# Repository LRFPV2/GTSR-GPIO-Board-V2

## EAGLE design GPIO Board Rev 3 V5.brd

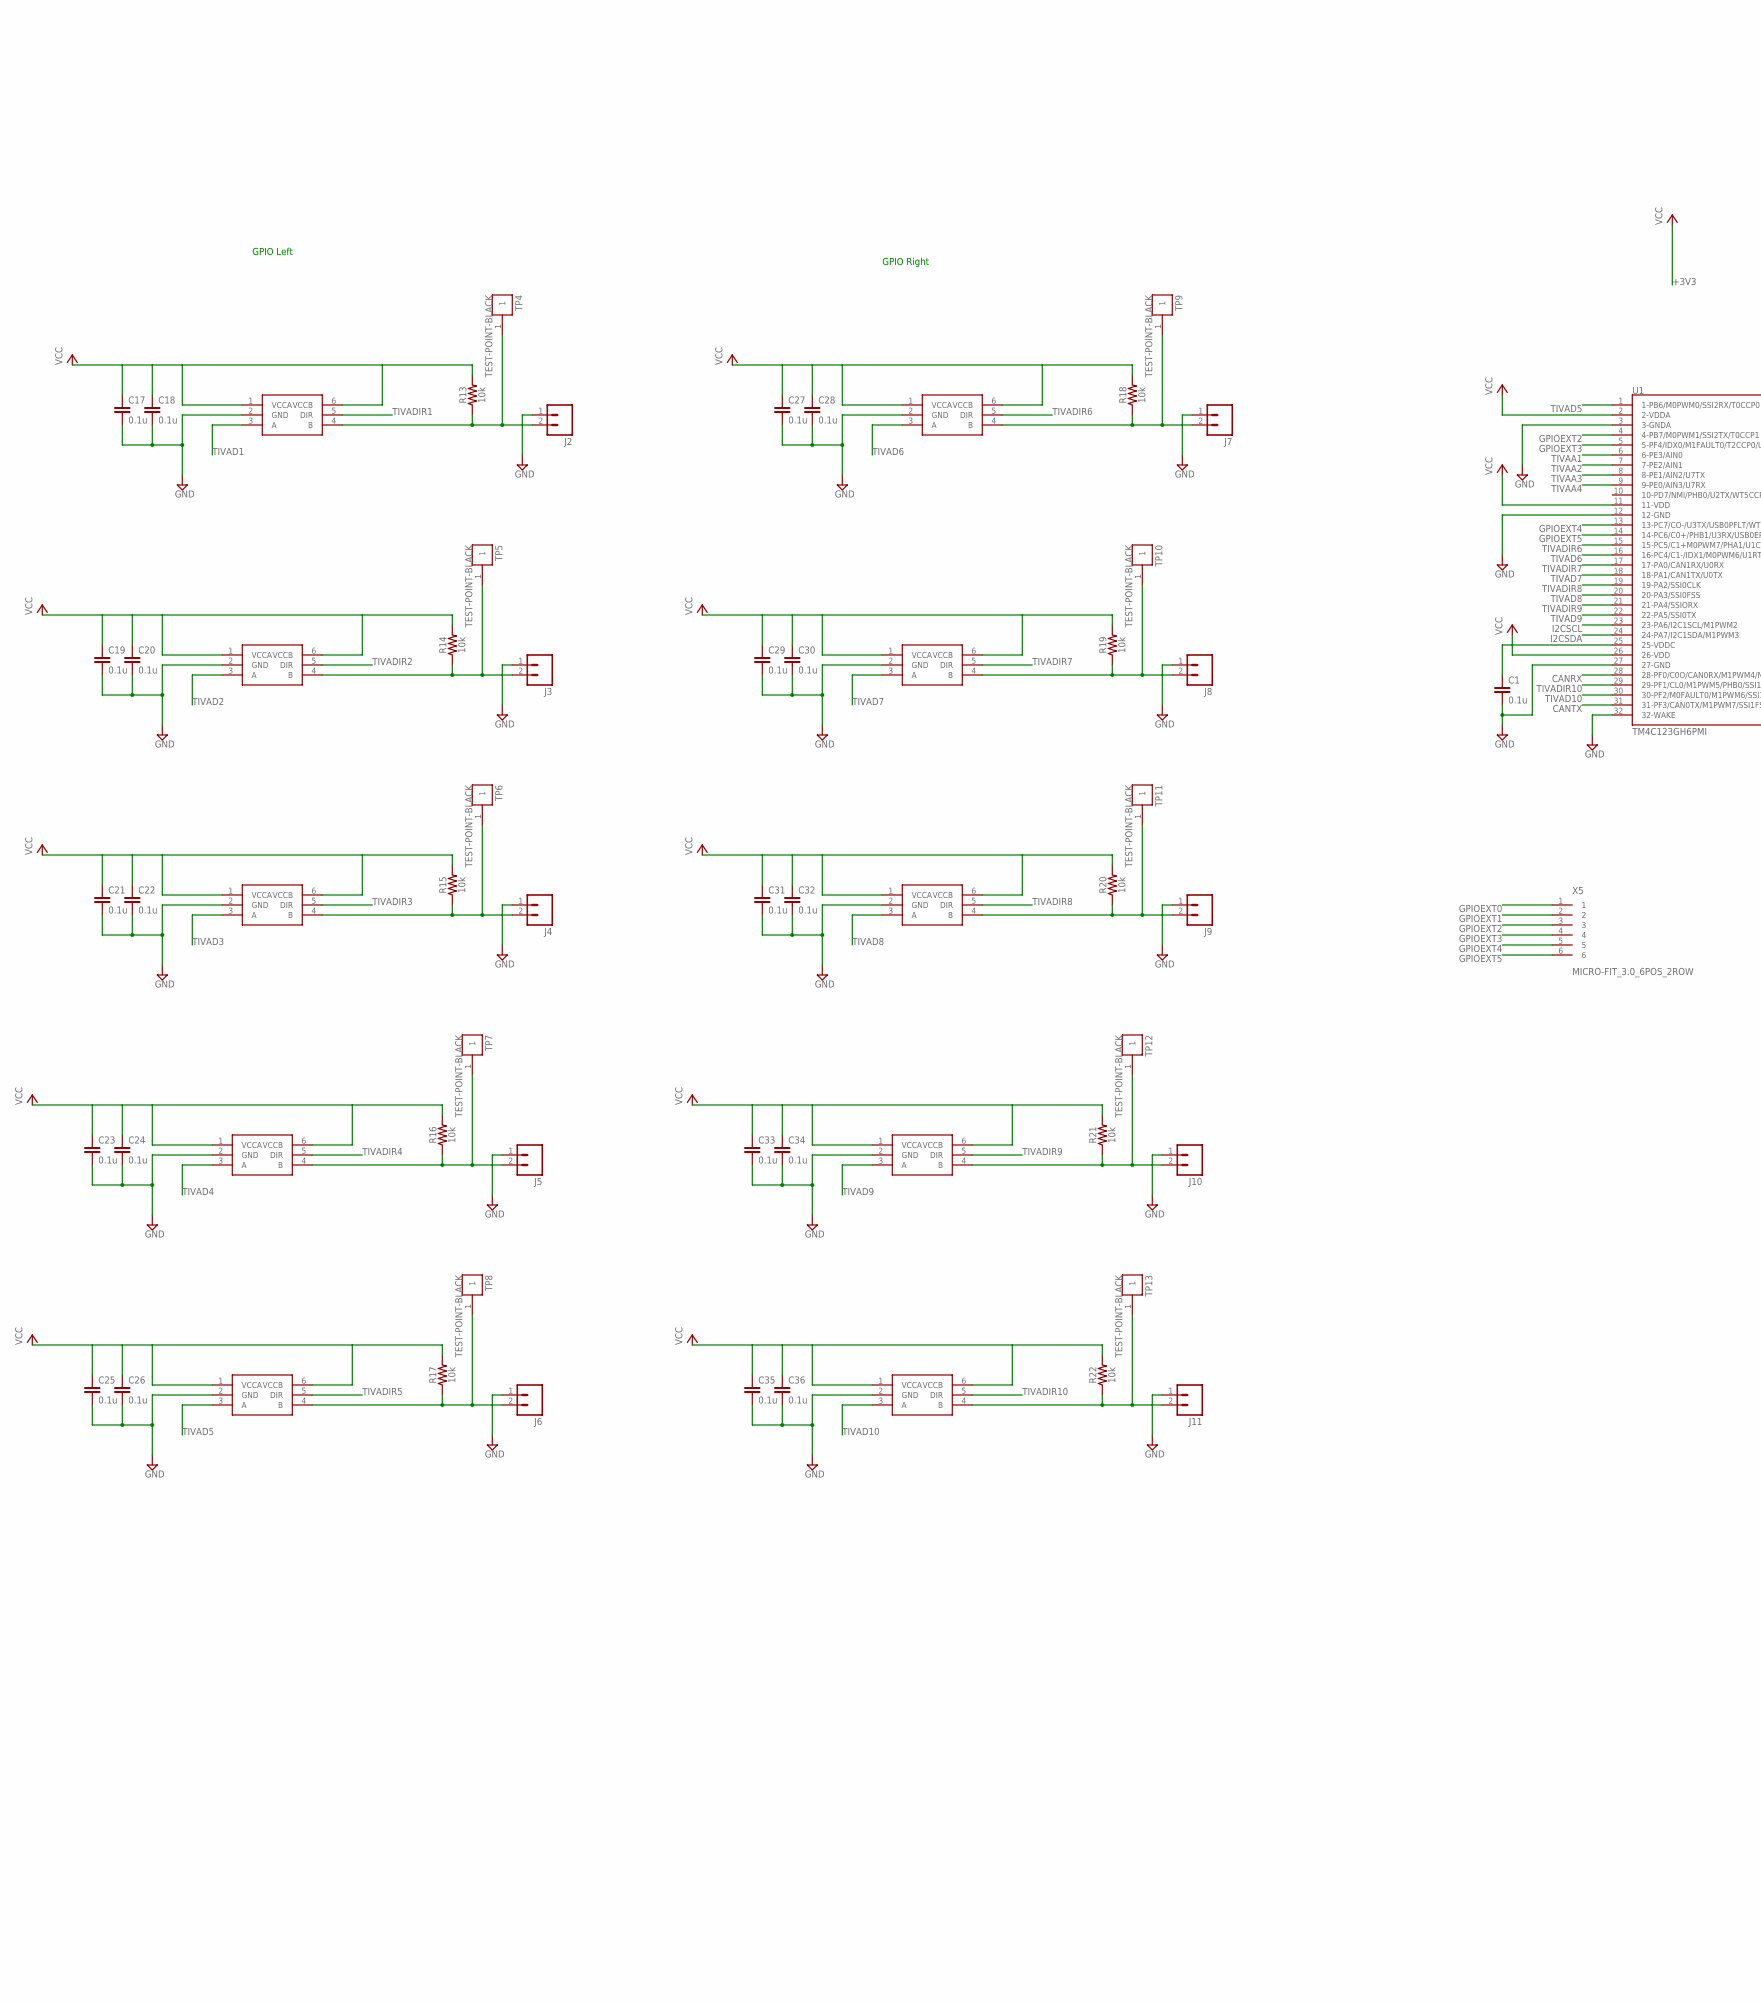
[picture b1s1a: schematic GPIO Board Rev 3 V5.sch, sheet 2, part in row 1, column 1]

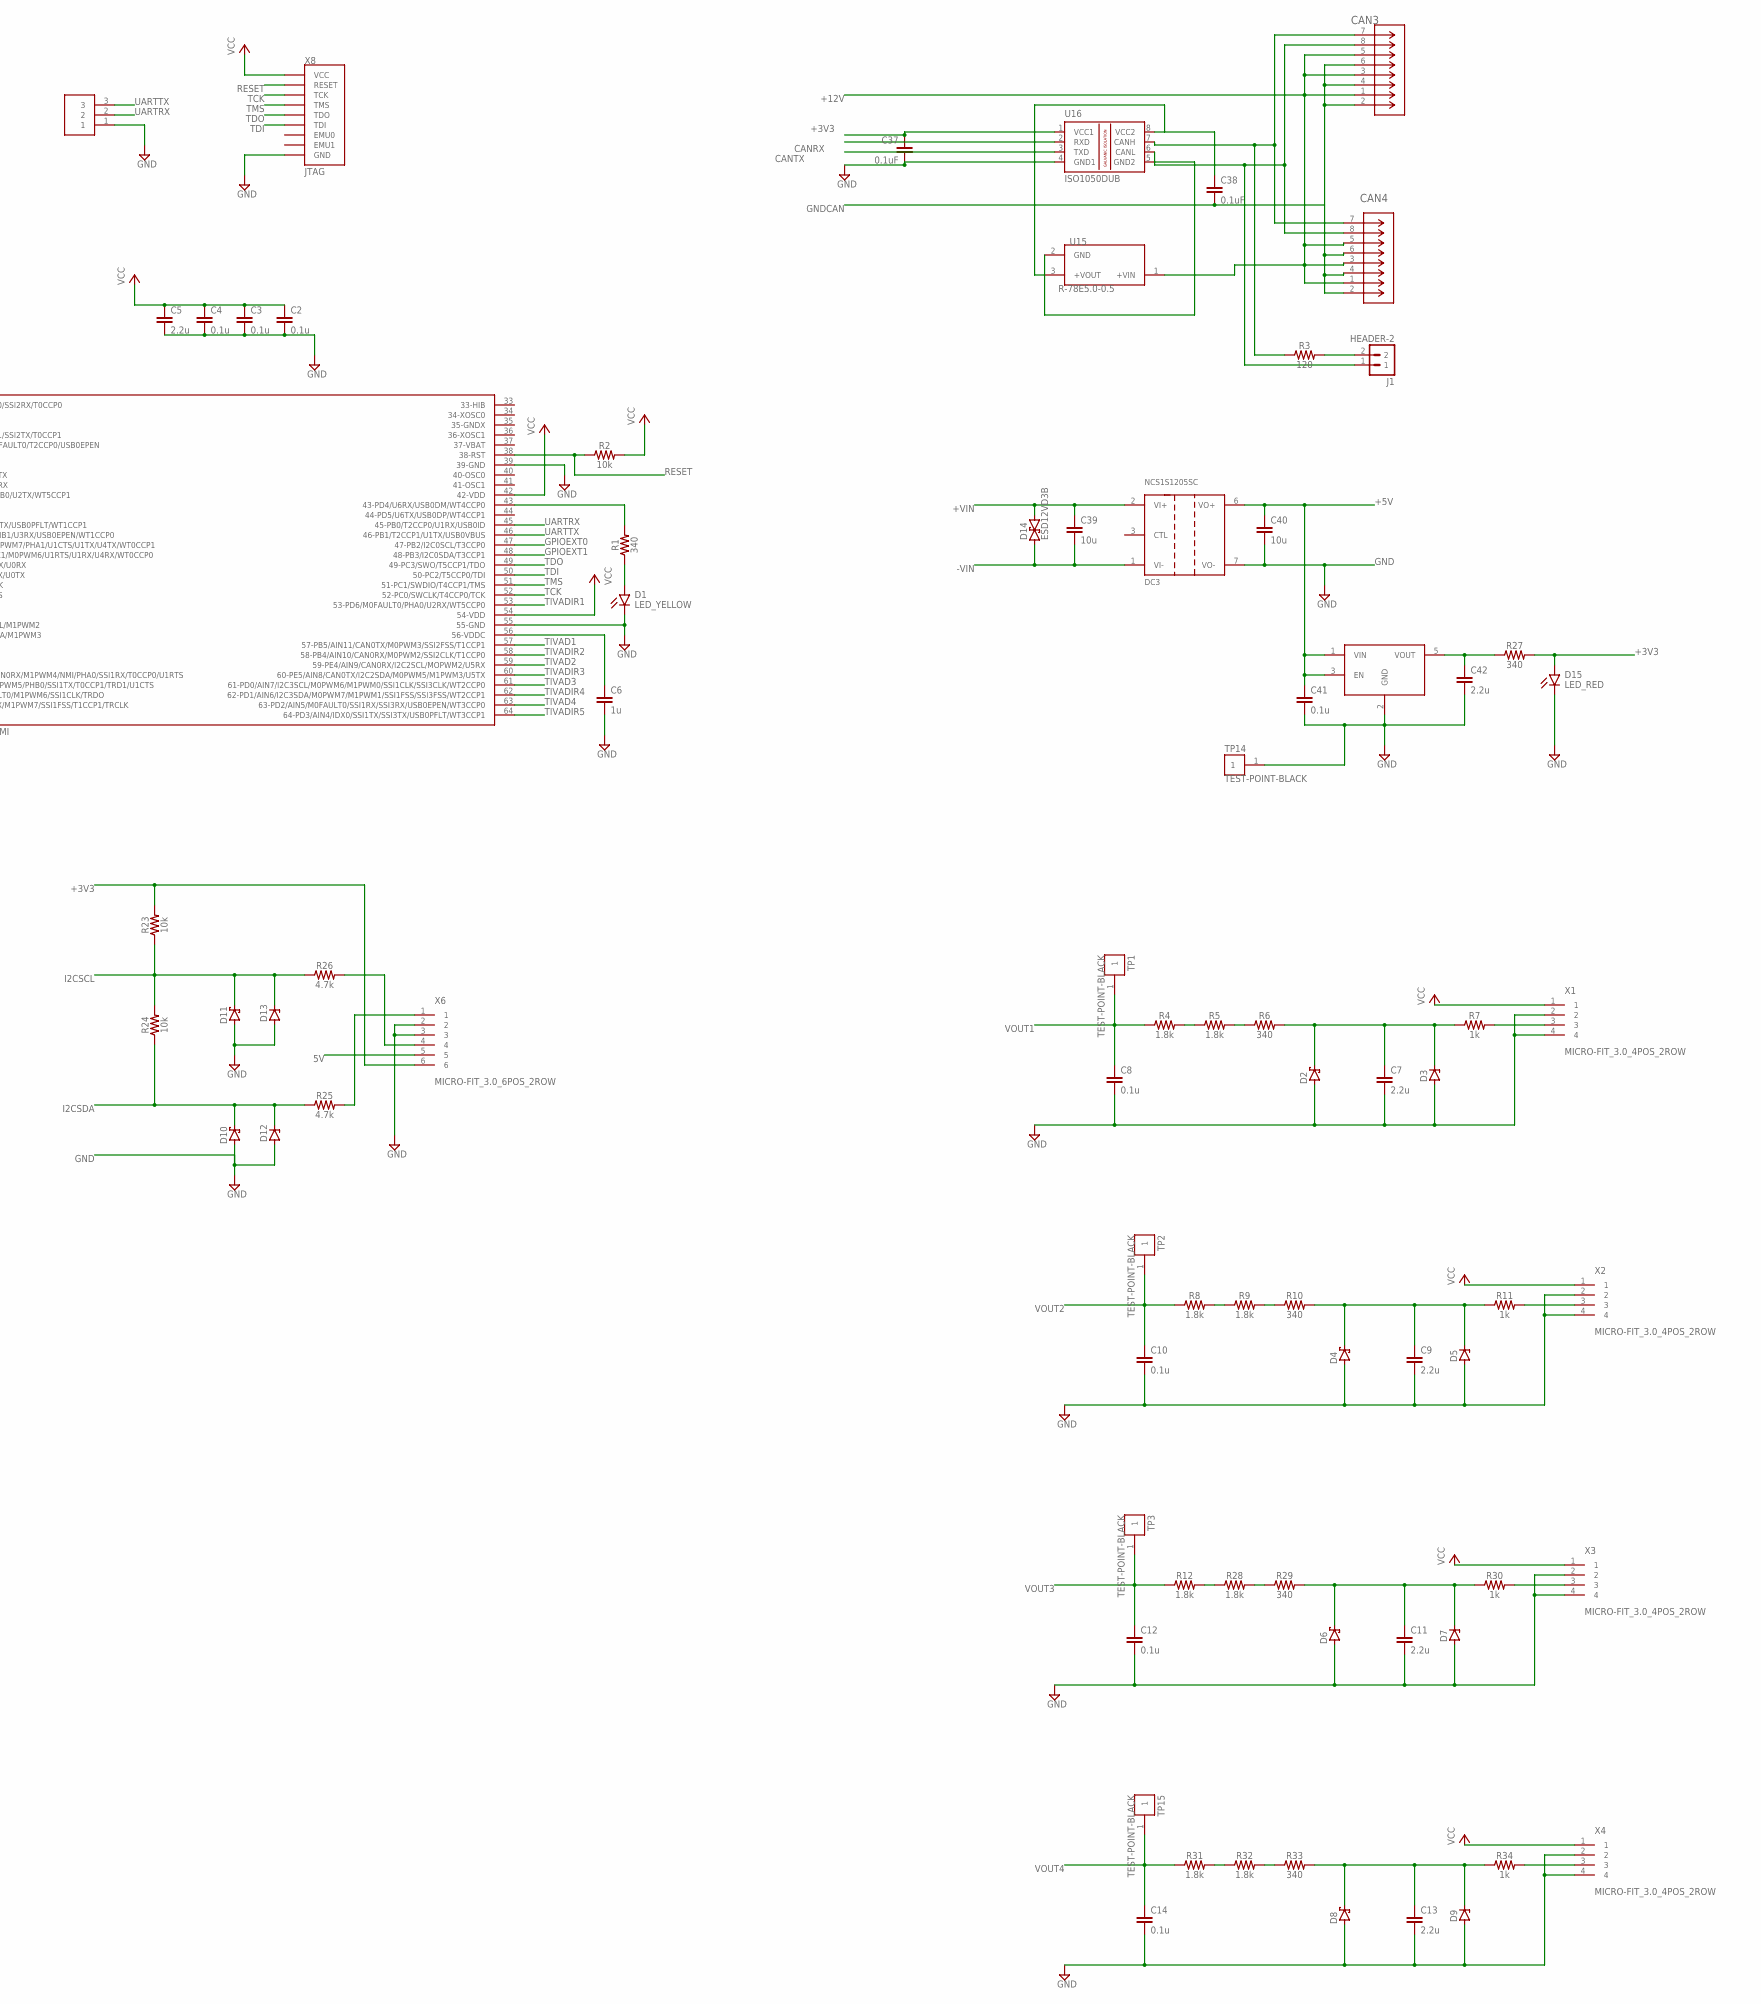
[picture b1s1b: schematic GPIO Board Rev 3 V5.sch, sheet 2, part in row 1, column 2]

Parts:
C1, C2, C3, C4, C8, C10, C12, C14, C41: 0.1u; C0603
C5, C7, C9, C11, C13: 2.2u; C0603
C6: 1u; C0603
C17, C18, C19, C20, C21, C22, C23, C24, C25, C26, C27, C28, C29, C30, C31, C32, C33, C34, C35, C36: 0.1u; C0402
C37: 0.1uF; C5B3.5
C38: 0.1uF; C2.5-4
C39, C40: 10u; 1206
C42: 2.2u; 0603
CAN3, CAN4: A-2004-2-4-LPS-N-R; CONN_4-LPS-N-R_ASM
D1: LED_YELLOW; LEDC1608X35N_FLAT-Y
D2, D4, D6, D8, D10, D11: SCHOTTKY-DIODESMD; SMB
D3, D5, D7, D9: ZENER-DIODESMB; SMB
D12, D13: ZENER-DIODESOT23; SOT23
D14: ESD12VD3B; SOD23
D15: LED_RED; LEDC2012X110N_FLAT-R
DC3: NCS1S1205SC; 7-SIP
DC4: NCV551SN33T1G; SOT23-5
J1: HEADER-2; HEADER-V-1X2
J2, J3, J4, J5, J6, J7, J8, J9, J10, J11: M02-JST-2-PTH-NO_SILK; JST-2-PTH-NS
R1, R6, R10, R27, R29, R33: 340; R0603
R2, R23, R24: 10k; R0603
R3: 120; R0603
R4, R5, R8, R9, R12, R28, R31, R32: 1.8k; R0603
R7, R11, R30, R34: 1k; R0603
R13, R14, R15, R16, R17, R18, R19, R20, R21, R22: 10k; 0603
R25, R26: 4.7k; R0603
TP1, TP2, TP3, TP4, TP5, TP6, TP7, TP8, TP9, TP10, TP11, TP12, TP13, TP14, TP15: TEST-POINT-BLACK; KEYSTONE_5001_0
U1: TM4C123GH6PMI; S-PQFP-G64
U5, U6, U7, U8, U9, U10, U11, U12, U13, U14: SN74LVC1T45-Q1; SC70
U15: R-78E5.0-0.5; CONV_R-78E5.0-0.5
U16: ISO1050DUB; DUB-R-PDSO-G8
U$2: HEADER-3; HEADER-V-1X3
X1, X2, X3, X4: MICRO-FIT_3.0_4POS_2ROW; 0430450412
X5, X6: MICRO-FIT_3.0_6POS_2ROW; 0430450612
X8: JTAG; HEADER-V-2X7

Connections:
5V: X6.5
+3V3: C37.2, D15.A, R23.2, R27.2, U16.1 (VCC1), X6.6
+5V: C40.1, C41.1, DC3.6 (VO+), DC4.1 (VIN), DC4.3 (EN)
+12V: CAN3.1, CAN3.3, CAN3.5, CAN4.1, CAN4.3, CAN4.5, U15.1 (+VIN)
+VIN: C39.1, D14.2, DC3.2 (VI+)
-VIN: C39.2, D14.1, DC3.1 (VI-)
CANRX: U1.28 (28-PF0/C0O/CAN0RX/M1PWM4/NMI/PHA0/SSI1R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), U16.2 (RXD)
CANTX: U1.31 (31-PF3/CAN0TX/M1PWM7/SSI1FSS/T1CCP1/TRC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), U16.3 (TXD)
GND: C1.2, C2.2, C3.2, C4.2, C5.2, C6.2, C7.2, C8.2, C9.2, C10.2, C11.2, C12.2, C13.2, C14.2, C17.2, C18.2, C19.2, C20.2, C21.2, C22.2, C23.2, C24.2, C25.2, C26.2, C27.2, C28.2, C29.2, C30.2, C31.2, C32.2, C33.2, C34.2, C35.2, C36.2, C37.1, C40.2, C41.2, C42.2, D1.C, D2.A, D3.A, D4.A, D5.A, D6.A, D7.A, D8.A, D9.A, D10.A, D11.A, D12.1 (A), D13.1 (A), D15.C, DC3.7 (VO-), DC4.2 (GND), J2.1, J3.1, J4.1, J5.1, J6.1, J7.1, J8.1, J9.1, J10.1, J11.1, TP14.1, U1.3 (3-GNDA), U1.12 (12-GND), U1.27 (27-GND), U1.32 (32-WAKE), U1.39 (39-GND), U1.55 (55-GND), U5.2 (GND), U6.2 (GND), U7.2 (GND), U8.2 (GND), U9.2 (GND), U10.2 (GND), U11.2 (GND), U12.2 (GND), U13.2 (GND), U14.2 (GND), U16.4 (GND1), U$2.1, X1.2, X1.4, X2.2, X2.4, X3.2, X3.4, X4.2, X4.4, X6.2, X6.3, X8.4 (GND), X8.6 (GND), X8.8 (GND), X8.10 (GND), X8.12 (GND)
GNDCAN: C38.2, CAN3.2, CAN3.4, CAN3.6, CAN4.2, CAN4.4, CAN4.6
GPIOEXT0: U1.47 (47-PB2/I2C0SCL/T3CCP0), X5.1
GPIOEXT1: U1.48 (48-PB3/I2C0SDA/T3CCP1), X5.2
GPIOEXT2: U1.4 (4-PB7/M0PWM1/SSI2TX/T0CCP1), X5.3
GPIOEXT3: U1.5 (5-PF4/IDX0/M1FAULT0/T2CCP0/USB0EPEN), X5.4
GPIOEXT4: U1.13 (13-PC7/CO-/U3TX/USB0PFLT/WT1CCP1), X5.5
GPIOEXT5: U1.14 (14-PC6/C0+/PHB1/U3RX/USB0EPEN/WT1CCP0), X5.6
I2CSCL: D11.C, D13.3 (C), R23.1, R24.2, R26.1, U1.23 (23-PA6/I2C1SCL/M1PWM2)
I2CSDA: D10.C, D12.3 (C), R24.1, R25.1, U1.24 (24-PA7/I2C1SDA/M1PWM3)
unnamed: R1.2, U1.43 (43-PD4/U6RX/USB0DM/WT4CCP0)
unnamed: D1.A, R1.1
unnamed: J1.2, R3.2
unnamed: CAN3.7, CAN4.7, R3.1, U16.7 (CANH)
unnamed: C1.1, U1.25 (25-VDDC)
unnamed: CAN3.8, CAN4.8, J1.1, U16.6 (CANL)
unnamed: R7.2, X1.3
unnamed: C6.1, U1.56 (56-VDDC)
unnamed: C7.1, D2.C, D3.C, R6.2, R7.1
unnamed: R5.2, R6.1
unnamed: R4.2, R5.1
unnamed: R11.2, X2.3
unnamed: C9.1, D4.C, D5.C, R10.2, R11.1
unnamed: R9.2, R10.1
unnamed: R8.2, R9.1
unnamed: R30.2, X3.3
unnamed: C11.1, D6.C, D7.C, R29.2, R30.1
unnamed: R28.2, R29.1
unnamed: R12.2, R28.1
unnamed: R34.2, X4.3
unnamed: J2.2, R13.1, TP4.1, U5.4 (B)
unnamed: J7.2, R18.1, TP9.1, U10.4 (B)
unnamed: J3.2, R14.1, TP5.1, U6.4 (B)
unnamed: J4.2, R15.1, TP6.1, U7.4 (B)
unnamed: J5.2, R16.1, TP7.1, U8.4 (B)
unnamed: J8.2, R19.1, TP10.1, U11.4 (B)
unnamed: J6.2, R17.1, TP8.1, U9.4 (B)
unnamed: J9.2, R20.1, TP11.1, U12.4 (B)
unnamed: J10.2, R21.1, TP12.1, U13.4 (B)
unnamed: J11.2, R22.1, TP13.1, U14.4 (B)
unnamed: R26.2, X6.4
unnamed: R25.2, X6.1
unnamed: C13.1, D8.C, D9.C, R33.2, R34.1
unnamed: R32.2, R33.1
unnamed: U15.2 (GND), U16.5 (GND2)
unnamed: C38.1, U16.8 (VCC2)
unnamed: C42.1, DC4.5 (VOUT), R27.1
unnamed: R31.2, R32.1
RESET: R2.1, U1.38 (38-RST), X8.2 (RESET)
TCK: U1.52 (52-PC0/SWCLK/T4CCP0/TCK), X8.9 (TCK), X8.11 (TCK)
TDI: U1.50 (50-PC2/T5CCP0/TDI), X8.3 (TDI)
TDO: U1.49 (49-PC3/SWO/T5CCP1/TDO), X8.7 (TDO)
TIVAA1: U1.6 (6-PE3/AIN0)
TIVAA2: U1.7 (7-PE2/AIN1)
TIVAA3: U1.8 (8-PE1/AIN2/U7TX)
TIVAA4: U1.9 (9-PE0/AIN3/U7RX)
TIVAD1: U1.57 (57-PB5/AIN11/CAN0TX/M0PWM3/SSI2FSS/T1CC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), U5.3 (A)
TIVAD2: U1.59 (59-PE4/AIN9/CAN0RX/I2C2SCL/MOPWM2/U5RX), U6.3 (A)
TIVAD3: U1.61 (61-PD0/AIN7/I2C3SCL/M0PWM6/M1PWM0/SSI1C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), U7.3 (A)
TIVAD4: U1.63 (63-PD2/AIN5/M0FAULT0/SSI1RX/SSI3RX/USB0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), U8.3 (A)
TIVAD5: U1.1 (1-PB6/M0PWM0/SSI2RX/T0CCP0), U9.3 (A)
TIVAD6: U1.16 (16-PC4/C1-/IDX1/M0PWM6/U1RTS/U1RX/U4RX/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), U10.3 (A)
TIVAD7: U1.18 (18-PA1/CAN1TX/U0TX), U11.3 (A)
TIVAD8: U1.20 (20-PA3/SSI0FSS), U12.3 (A)
TIVAD9: U1.22 (22-PA5/SSI0TX), U13.3 (A)
TIVAD10: U1.30 (30-PF2/M0FAULT0/M1PWM6/SSI1CLK/TRDO), U14.3 (A)
TIVADIR1: U1.53 (53-PD6/M0FAULT0/PHA0/U2RX/WT5CCP0), U5.5 (DIR)
TIVADIR2: U1.58 (58-PB4/AIN10/CAN0RX/M0PWM2/SSI2CLK/T1CC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), U6.5 (DIR)
TIVADIR3: U1.60 (60-PE5/AIN8/CAN0TX/I2C2SDA/M0PWM5/M1PWM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), U7.5 (DIR)
TIVADIR4: U1.62 (62-PD1/AIN6/I2C3SDA/M0PWM7/M1PWM1/SSI1F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), U8.5 (DIR)
TIVADIR5: U1.64 (64-PD3/AIN4/IDX0/SSI1TX/SSI3TX/USB0PFLT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), U9.5 (DIR)
TIVADIR6: U1.15 (15-PC5/C1+M0PWM7/PHA1/U1CTS/U1TX/U4TX/W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), U10.5 (DIR)
TIVADIR7: U1.17 (17-PA0/CAN1RX/U0RX), U11.5 (DIR)
TIVADIR8: U1.19 (19-PA2/SSI0CLK), U12.5 (DIR)
TIVADIR9: U1.21 (21-PA4/SSIORX), U13.5 (DIR)
TIVADIR10: U1.29 (29-PF1/CL0/M1PWM5/PHB0/SSI1TX/T0CCP1/TR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), U14.5 (DIR)
TMS: U1.51 (51-PC1/SWDIO/T4CCP1/TMS), X8.1 (TMS)
UARTRX: U1.45 (45-PB0/T2CCP0/U1RX/USB0ID), U$2.2
UARTTX: U1.46 (46-PB1/T2CCP1/U1TX/USB0VBUS), U$2.3
VCC: C2.1, C3.1, C4.1, C5.1, C18.1, C20.1, C22.1, C24.1, C26.1, C28.1, C30.1, C32.1, C34.1, C36.1, R2.2, R13.2, R14.2, R15.2, R16.2, R17.2, R18.2, R19.2, R20.2, R21.2, R22.2, U1.2 (2-VDDA), U1.11 (11-VDD), U1.26 (26-VDD), U1.42 (42-VDD), U1.54 (54-VDD), U5.6 (VCCB), U6.6 (VCCB), U7.6 (VCCB), U8.6 (VCCB), U9.6 (VCCB), U10.6 (VCCB), U11.6 (VCCB), U12.6 (VCCB), U13.6 (VCCB), U14.6 (VCCB), X1.1, X2.1, X3.1, X4.1, X8.5 (VCC)
VOUT1: C8.1, R4.1, TP1.1
VOUT2: C10.1, R8.1, TP2.1
VOUT3: C12.1, R12.1, TP3.1
VOUT4: C14.1, R31.1, TP15.1

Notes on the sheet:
GPIO Left
GPIO Right

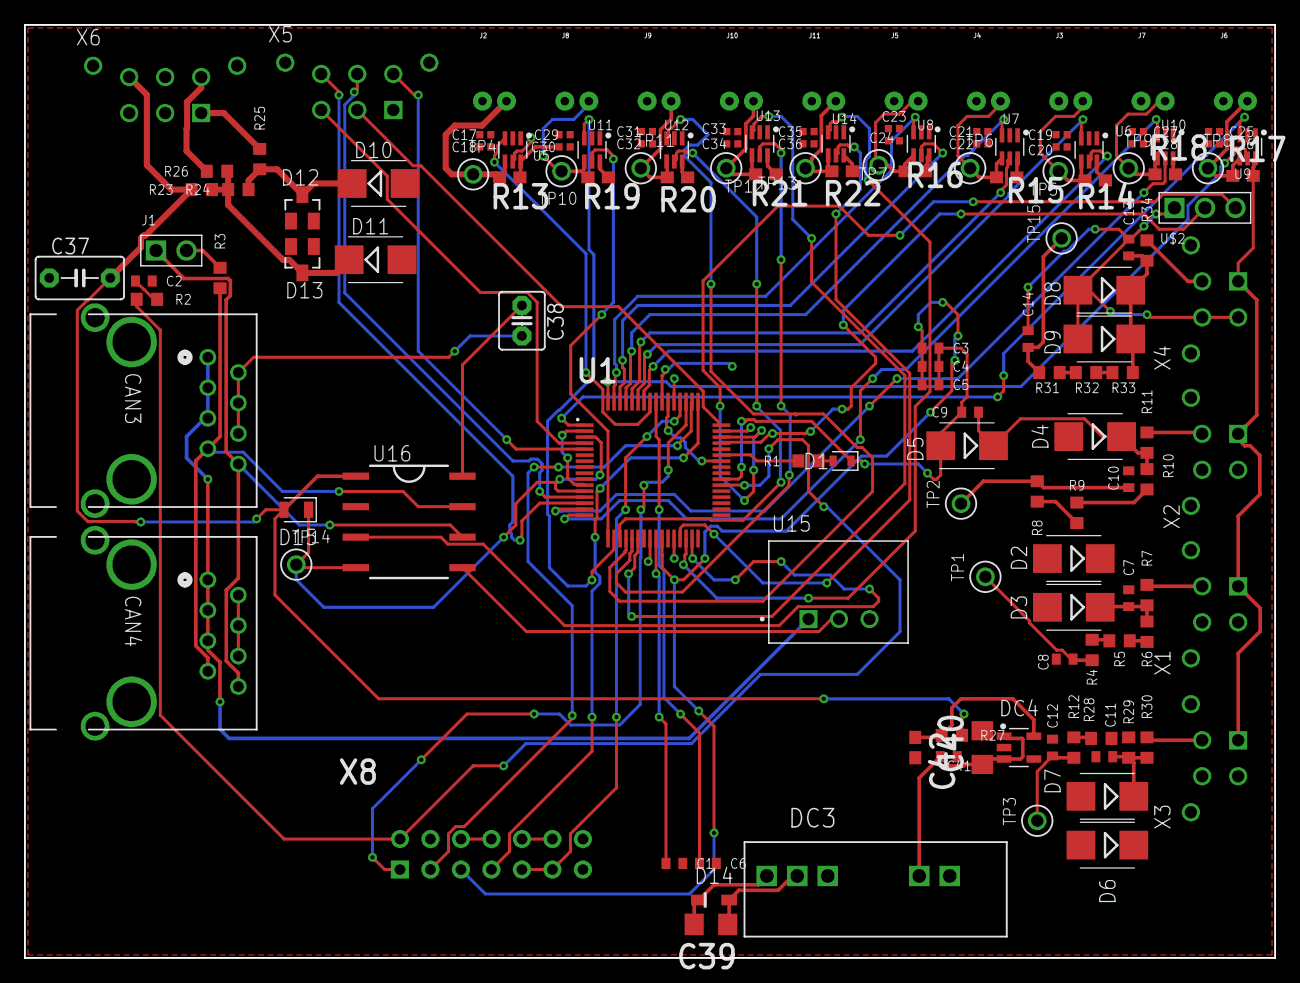
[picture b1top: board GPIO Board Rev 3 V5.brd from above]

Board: 2 copper layers, 104.1 x 77.7 mm, 140 parts (0 on the bottom side), 87 nets.

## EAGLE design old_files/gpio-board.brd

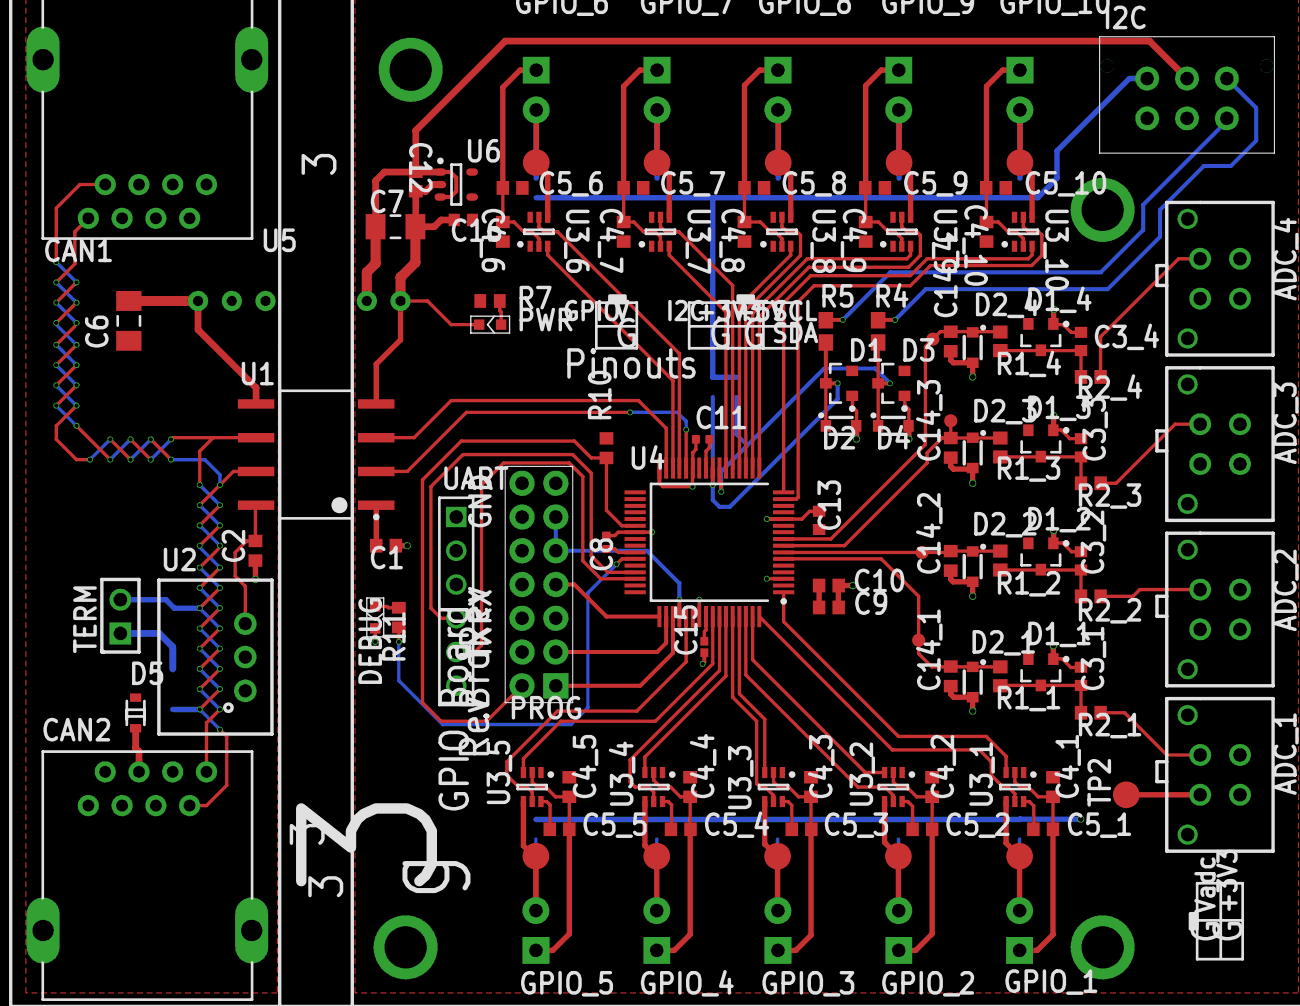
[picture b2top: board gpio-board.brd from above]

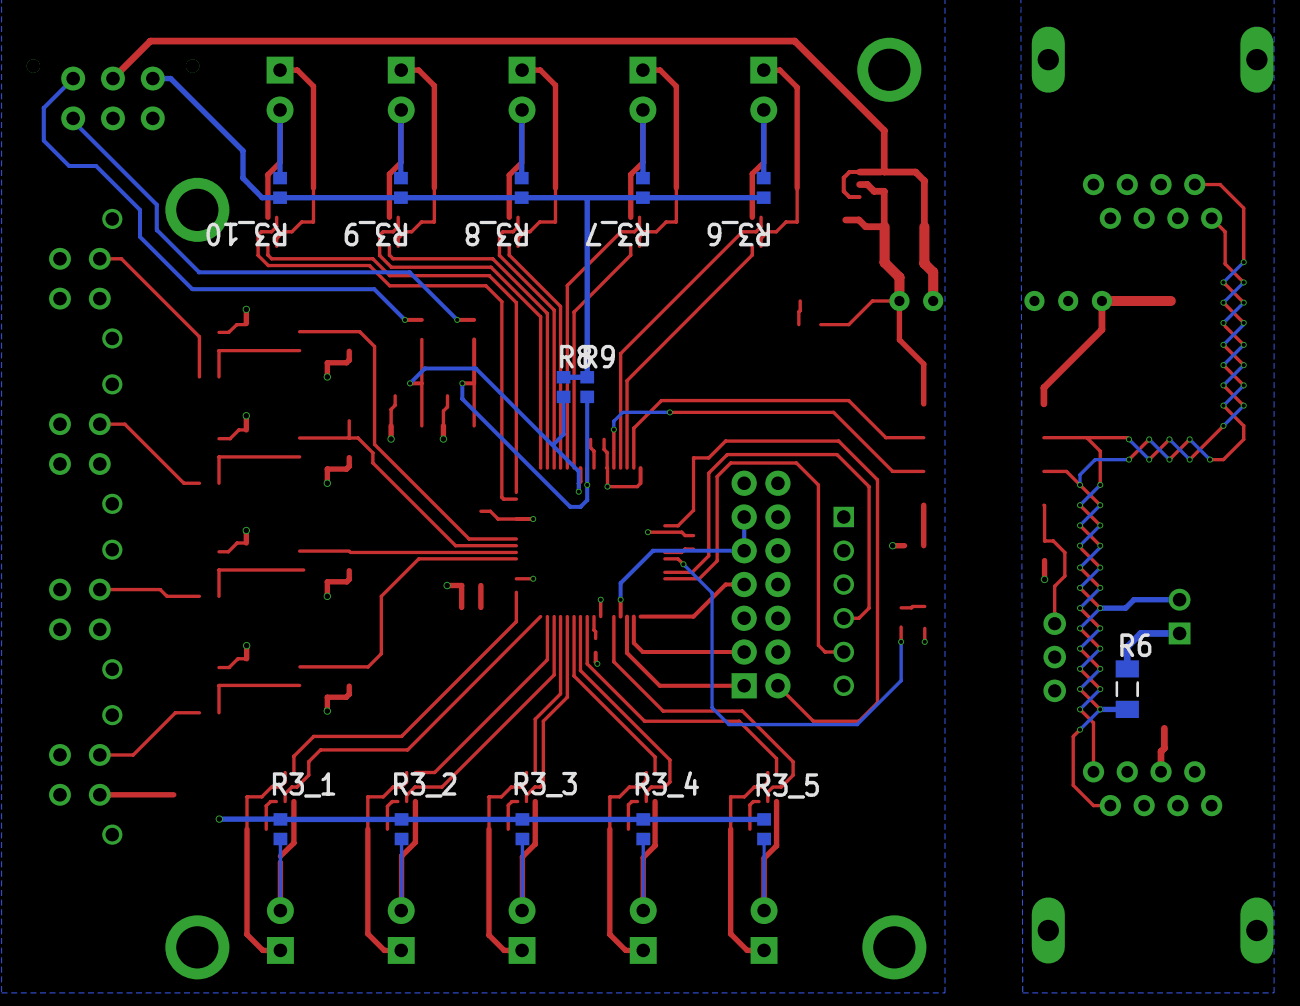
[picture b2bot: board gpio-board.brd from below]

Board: 2 copper layers, 135 parts (13 on the bottom side), 5 nets.

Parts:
ADC_1, ADC_2, ADC_3, ADC_4: Molex_43045-0412; PCB-DEII51DOH0YLT05YINNA-1_1PRIMARY
C1, C2, C4_1, C4_2, C4_3, C4_4, C4_5, C4_6, C4_7, C4_8, C4_9, C4_10, C5_1, C5_2, C5_3, C5_4, C5_5, C5_6, C5_7, C5_8, C5_9, C5_10, C10, C12: 0.1uF; CAPC1608X90X35ML10T15_1PRIMARY
C3_1, C3_2, C3_3, C3_4, C13, C16: Murata_GRT188C8YA225KE13D; PCB-D6AJCE48RKQ1HIVISM3Y-1_1PRIMARY
C6, C7: TDK_CGA5L1X7R1E106K160AC; CAPC3216X94X50ML20T25_1PRIMARY
C8, C11: Murata_GCM155R71C104KA55D; PCB-RS1RQ4I227AAQDZS4V5U-1_1PRIMARY
C9, C14_1, C14_2, C14_3, C14_4: Murata_GCM188R72A103KA37D; CAPC1608X90X35ML10T15_1PRIMARY
C15: Cap; CAPC1005X55X25NL05T10_1PRIMARY
CAN1: Assmann_A-2004-2-4-LPS-N-R; PCB-617644-1_1PRIMARY
CAN2: Assmann_A-2004-2-4-LPS-N-R; PCB-617644-1_2PRIMARY
D1, D1_1, D1_2, D1_3, D1_4, D3: BZX84B5V1LT1G; PCB-826HQ61C5HRMK636OS7I-1_1PRIMARY
D2, D2_1, D2_2, D2_3, D2_4, D4: CUS520,H3F; PCB-LEB5SPC6MITBTSBK5TX6-1_1PRIMARY
D5: ESD12VD3B-TP; PCB-I0FBSBJYI21MW6A9P1H2-1_1PRIMARY
DEBUG: LED; PCB-49LZSAGIYOPML94DMXSO-1_1PRIMARY
DUMMY1, DUMMY2, DUMMY3, DUMMY4: P:EX190Y190D1251
GPIO_1, GPIO_2, GPIO_3, GPIO_4, GPIO_5, GPIO_6, GPIO_7, GPIO_8, GPIO_9, GPIO_10: Molex_0430450212; PCB-EBANZHXDR8KRO84SZ5US-1_1PRIMARY
I2C: Molex_43045-0613; PCB-8Y24NF48ZEBEN9QZAJWL-1_1PRIMARY
PROG: JTAG; PCB-VVNC32FXY3RXRFE3EZXP-1_1PRIMARY
PWR: LED; PCB-49LZSAGIYOPML94DMXSO-1_1PRIMARY
R1_1, R1_2, R1_3: Panasonic_ERJ-3EKF3901V; PCB-PZR69ND8R73CHJ6EB9MQ-1_1PRIMARY
R1_4: Panasonic_ERJ-3EKF3901V; PCB-PZR69ND8R73CHJ6EB9MQ-1_2PRIMARY
R2_1, R2_2, R2_3, R2_4: Res1; PCB-2KQ0Q186M0A2Q7QR8G59-1_1PRIMARY
R3_1, R3_2, R3_3, R3_4, R3_5, R3_6, R3_7, R3_8, R3_9, R3_10, R8, R9, R10: Res1; PCB-0L9YF81OQ53TI1Q912G7-1_1PRIMARY
R4, R5: Panasonic_ERJ-3GEYJ472V; PCB-2RBVLBEZ7GB2PG7HRA0P-1_1PRIMARY
R6: Panasonic_ERJ-8GEYJ121V; RESC3216X70X50ML05T20_1PRIMARY
R7, R11: Panasonic_ERJ-3GEYJ331V; RESC1608X55X30ML15T15_1PRIMARY
TERM: Samtec_TSW-102-07-G-S; PCB-YWUYZLJSEFP2PSQ2ZQH0-1_1PRIMARY
TP1_1, TP1_2, TP1_3, TP1_4, TP1_5, TP1_6, TP1_7, TP1_8, TP1_9, TP1_10, TP2: Test_Pad; PCB-KZRZ332CMU8NBWTQD8UW-1_2PRIMARY
TP3_1, TP3_2, TP3_3, TP3_4: Test_Pad; PCB-KZRZ332CMU8NBWTQD8UW-1_1PRIMARY
U1: TI-ISO1050-SOP_DUB-8; PCB-DV9O3AVLIIB4ETIW6Y3O-1_1PRIMARY
U2: Recom_Power_R-78E5.0-0.5; PCB-YSM4WBM1VT1WQ7B8B8LJ-1_1PRIMARY
U3_1, U3_2, U3_3, U3_4, U3_5, U3_6, U3_7, U3_8, U3_9, U3_10: SN74LVC1T45QDCKRQ1; PCB-U1BF8RHDO4XCF1EB4J2A-1_1PRIMARY
U4: TM4C123GH6PMIR; TI-PM-64_V_1PRIMARY
U5: NCS1S2405SC; PCB-KC945RGRSQCX7MCRR5DR-1_1PRIMARY
U6: ON_Semiconductor_NCV551SN33T1G; PCB-DJS7SZGBAKRF40B0AEIK-1_1PRIMARY
UART: SYM-eb5f2251e9703498-3; PCB-EWXEYP75JDH83BBP67M9-1_1PRIMARY

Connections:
CANH: CAN1.7, CAN2.7
NETC2_2: CAN2.2, CAN2.4, CAN2.6
NETC6_2: CAN2.1, CAN2.3, CAN2.5
NETC15_2: C15.2, U4.56
NETR10_2: R11.2, U4.43

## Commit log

2021-09-20 9/20/21
    Progress so far
2021-09-20 1
    1
2021-09-26 V5
    this should be the barebones schematic.
2021-09-26 final schematic 1
2021-10-03 10.3.21
    Schematic is done. Most changes have been made. We are in the process of doing board layout.

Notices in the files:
parts and their libraries:
COPYRIGHT: Copyright (C) 2021 Ultra Librarian. All rights reserved.
